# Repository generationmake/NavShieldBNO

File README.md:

# NavShieldBNO
Navigation shield for Arduino with Bosch BNO055, BNO080 or BNO085

## pin usage

### Arduino MKR connector CN1

| **Pin** | **Pin Name** | **Signal**    | **Description**                  |
|:-------:|:------------:|:-------------:|:--------------------------------:|
| 1       | AREF         |               |                                  |
| 2       | DAC0/A0      |               |                                  |
| 3       | A1           |               |                                  |
| 4       | A2           |               |                                  |
| 5       | A3           |               |                                  |
| 6       | A4           |               |                                  |
| 7       | A5           | WAKE_2        | option 2 for WAKE from BNO085    |
| 8       | A6           |               |                                  |
| 9       | 0            |               |                                  |
| 10      | 1            | WAKE_1        | option 1 for WAKE from BNO085    |
| 11      | 2            | BMP388_CS     | chip select for BMP388           |
| 12      | 3            |               |                                  |
| 13      | 4            |               |                                  |
| 14      | 5            | BNO085_CS     | chip select for BNO085           |
| 15      | 6            | BMP388_INT    | interrupt from BMP388            |
| 16      | 7            | BNO085_INT    | interrupt from BNO085            |
| 17      | 8/MOSI       | SPI_MOSI      | to sensors if SPI option is used |
| 18      | 9/SCK        | SPI_SCK       | to sensors if SPI option is used |
| 19      | 10/MISO      | SPI_MISO      | to sensors if SPI option is used |
| 20      | 11/SDA       | I2C_SDA       | to sensors if I2C option is used |
| 21      | 12/SCL       | I2C_SCL       | to sensors if I2C option is used |
| 22      | 13/RX        | SERIAL_RX     | to connector CN3                 |
| 23      | 14/TX        | SERIAL_TX     | to connector CN3                 |
| 24      | RESET        | RESET         | Reset for BNO085                 |
| 25      | GND          | GND           |                                  |
| 26      | VCC          | 3V3-rail      | supply voltage for board         |
| 27      | VIN          |               |                                  |
| 28      | 5V0          |               |                                  |

### Qwiic I2C connector CN2

compatible to Sparkfun Qwiic. JST SH 1mm 4-pin.

| **Pin** | **Signal**    | **Description**                  |
|:-------:|:-------------:|:--------------------------------:|
| 1       | GND           |                                  |
| 2       | VCC           |                                  |
| 3       | I2C_SDA       |                                  |
| 4       | I2C_SCL       |                                  |

### serial connector CN3

JST SH 1mm 4-pin.

| **Pin** | **Signal**    | **Description**                  |
|:-------:|:-------------:|:--------------------------------:|
| 1       | GND           |                                  |
| 2       | VCC           |                                  |
| 3       | SERIAL_TX     |                                  |
| 4       | SERIAL_RX     |                                  |

## PCB

### Top

### Bottom

## Variants

It is possible to mount a BNO055 instead of the BNO085. The BNO055 only supports the I2C interface.

### BOM changes

The following parts need to be changed:

| part | BNO085 variant | BNO055 variant |
|:----:|:--------------:|:--------------:|
| R1   | 10k            | DNI            |
| R2   | 10k            | DNI            |
| R5   | 10k            | DNI            |
| R6   | DNI            | 10k            |
| R7   | 10k            | DNI            |
| R8   | DNI            | 10k            |
| R10  | DNI            | 0R             |
| R11  | DNI            | 0R             |
| R12  | DNI            | 0R             |
| R13  | 0R             | DNI            |
| R14  | 0R             | DNI            |
| R15  | 0R             | DNI            |
| R16  | 0R             | DNI            |
| C8   | 100nF          | DNI            |
| C9   | 100nF          | DNI            |
| C10  | 100nF          | DNI            |
| C11  | 100nF          | DNI            |
| U1   | BNO085         | BMP055         |
| U3   | BMP280         | DNI            |
| U4   | BME280         | DNI            |
| U5   | VCNL4040       | DNI            |

## Resources

### Datasheets

 * *BNO080* https://cdn.sparkfun.com/assets/2/b/9/0/6/DS-14686-BNO080.pdf
 * *BMP388* https://www.bosch-sensortec.com/media/boschsensortec/downloads/datasheets/bst-bmp388-ds001.pdf
 * *BNO055* https://www.bosch-sensortec.com/media/boschsensortec/downloads/datasheets/bst-bno055-ds000.pdf

### Arduino Libraries

* [107-Arduino-BNO085](https://github.com/107-systems/107-Arduino-BNO085)
* [107-Arduino-BMP388](https://github.com/107-systems/107-Arduino-BMP388)

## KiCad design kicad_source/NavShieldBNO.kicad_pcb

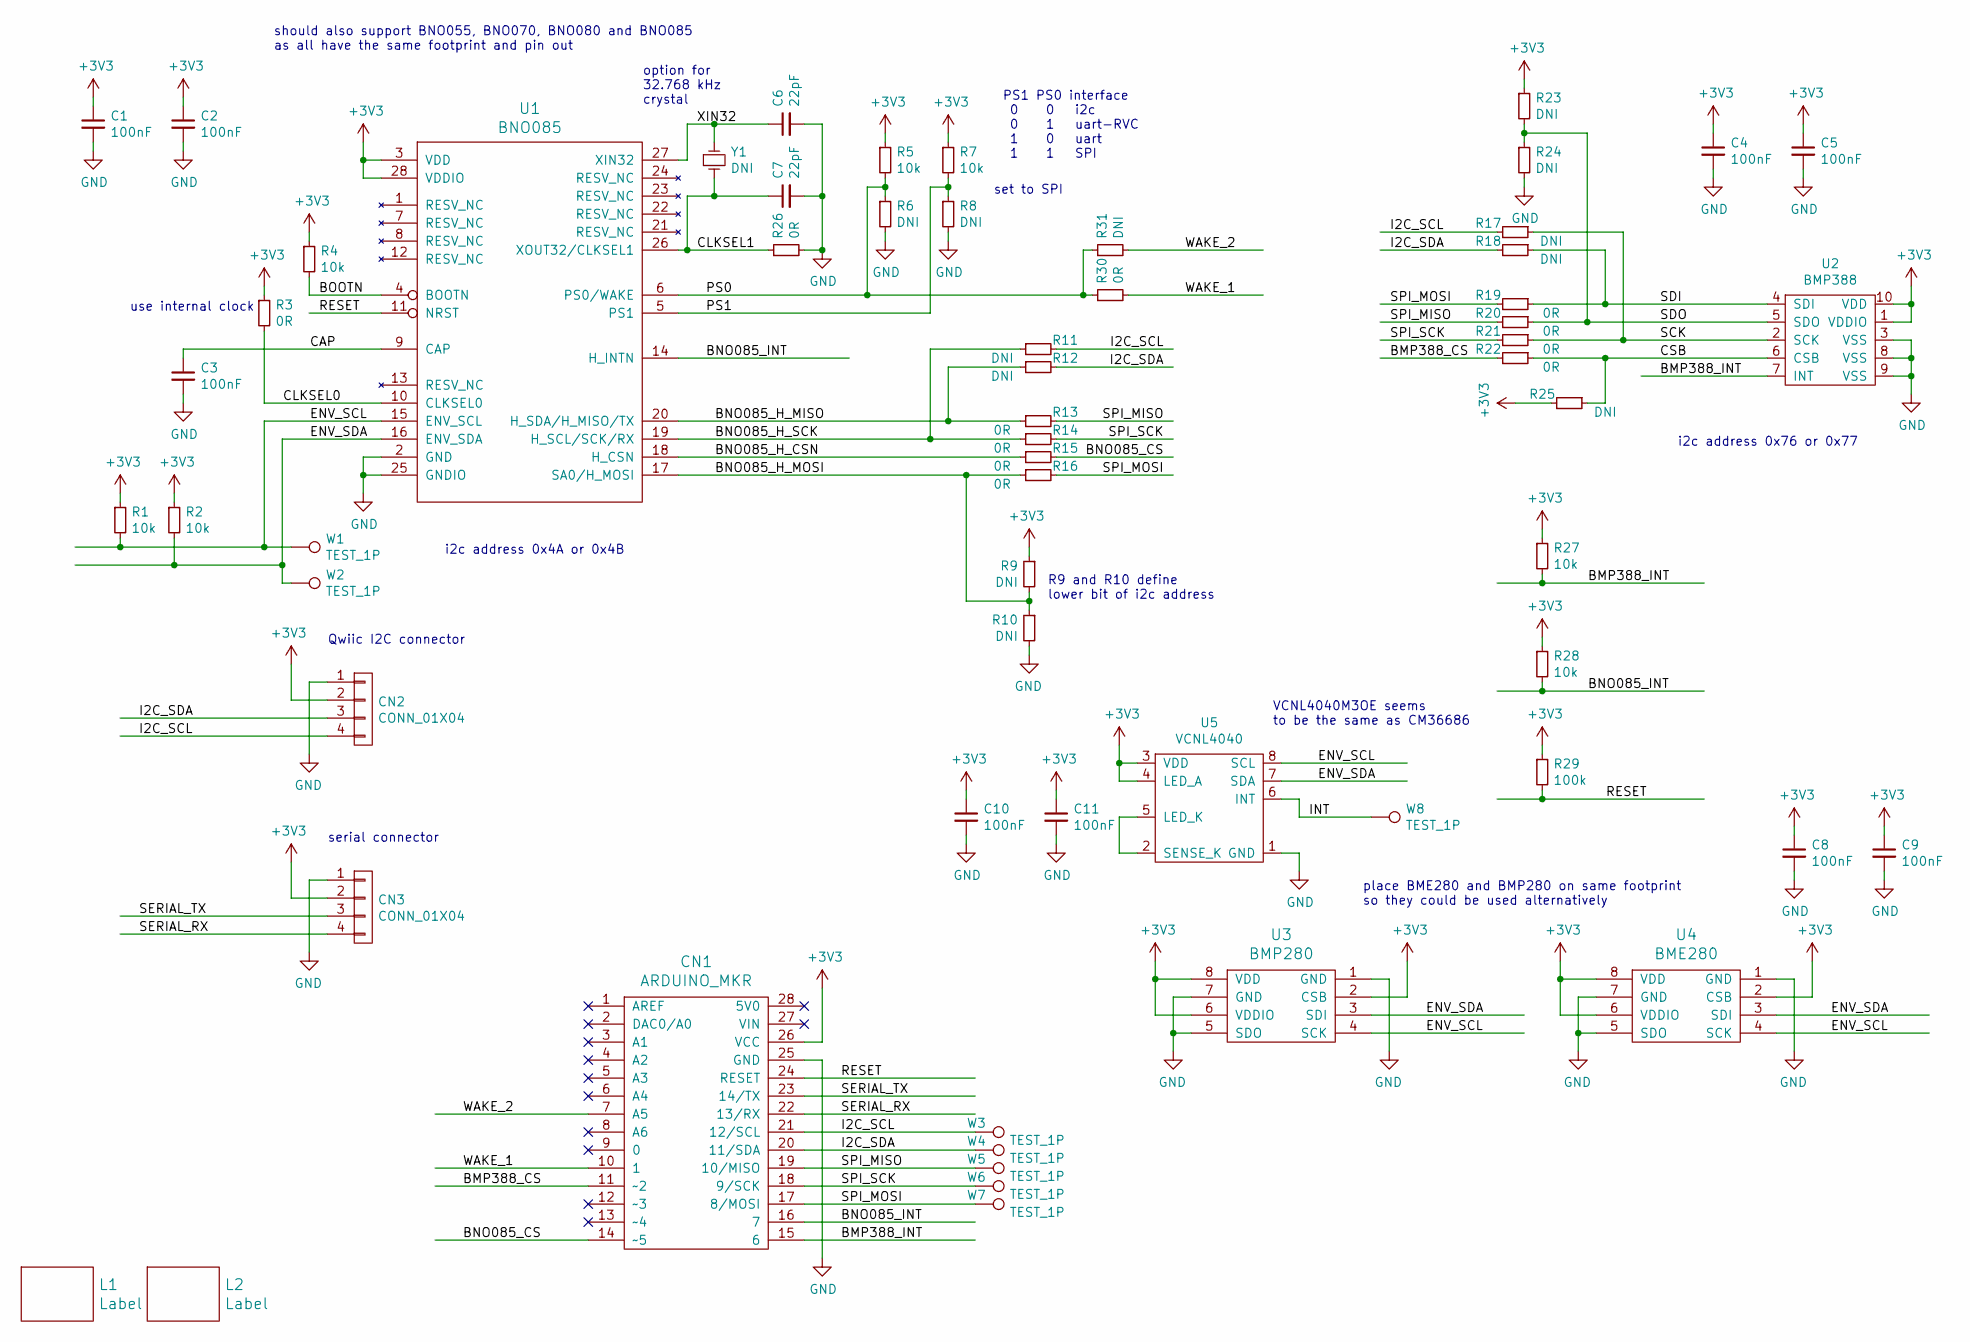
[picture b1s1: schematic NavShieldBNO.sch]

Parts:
C1, C2, C3, C4, C5, C8, C9, C10, C11: 100nF; C_0603
C6, C7: 22pF; C_0603
CN1: ARDUINO_MKR; ARDUINO_MKR_HOLES
CN2, CN3: CONN_01X04; Connectors_JST_SM04B-SRSS-TB
L1: Label; generationmake_small_solder
L2: Label; generationmake_logo
R1, R2, R4, R5, R7, R27, R28: 10k; R_0603
R3, R13, R14, R15, R16, R19, R20, R21, R22, R26, R30: 0R; R_0603
R6, R8, R9, R10, R11, R12, R17, R18, R23, R24, R25, R31: DNI; R_0603
R29: 100k; R_0603
U1: BNO085; LGA-28-5832
U2: BMP388
U3: BMP280
U4: BME280
U5: VCNL4040
W1, W2, W3, W4, W5, W6, W7, W8: TEST_1P; SolderWirePad_single_1mmSMD
Y1: DNI; Crystal_SMD_3.2x1.5mm_2Pad

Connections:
+3V3: C1.1, C2.1, C4.1, C5.1, C8.1, C9.1, C10.1, C11.1, CN1.26 (VCC), CN2.2, CN3.2, R1.1, R2.1, R3.1, R4.1, R5.1, R7.1, R9.1, R23.1, R25.2, R27.1, R28.1, R29.1, U1.3 (VDD), U1.28 (VDDIO), U2.1 (VDDIO), U2.10 (VDD), U3.2 (CSB), U3.6 (VDDIO), U3.8 (VDD), U4.2 (CSB), U4.6 (VDDIO), U4.8 (VDD), U5.3 (VDD), U5.4 (LED_A)
/BMP388_CS: CN1.11 (~~2), R22.2
/BMP388_INT: CN1.15 (6), R27.2, U2.7 (INT)
/BNO085_CS: CN1.14 (~~5), R15.2
/BNO085_H_CSN: R15.1, U1.18 (H_CSN)
/BNO085_H_MISO: R12.1, R13.1, U1.20 (H_SDA/H_MISO/TX)
/BNO085_H_MOSI: R9.2, R10.1, R16.1, U1.17 (SA0/H_MOSI)
/BNO085_H_SCK: R11.1, R14.1, U1.19 (H_SCL/SCK/RX)
/BNO085_INT: CN1.16 (7), R28.2, U1.14 (H_INTN)
/BOOTN: R4.2, U1.4 (BOOTN)
/CAP: C3.1, U1.9 (CAP)
/CLKSEL0: R3.2, U1.10 (CLKSEL0)
/CLKSEL1: C7.1, R26.1, U1.26 (XOUT32/CLKSEL1), Y1.2
/CSB: R22.1, R25.1, U2.6 (CSB)
/ENV_SCL: R1.2, U1.15 (ENV_SCL), U3.4 (SCK), U4.4 (SCK), U5.8 (SCL), W1.1
/ENV_SDA: R2.2, U1.16 (ENV_SDA), U3.3 (SDI), U4.3 (SDI), U5.7 (SDA), W2.1
/I2C_SCL: CN1.21 (12/SCL), CN2.4, R11.2, R17.2, W3.1
/I2C_SDA: CN1.20 (11/SDA), CN2.3, R12.2, R18.2, W4.1
/INT: U5.6 (INT), W8.1
/PS0: R5.2, R6.1, R30.1, R31.1, U1.6 (PS0/WAKE)
/PS1: R7.2, R8.1, U1.5 (PS1)
/RESET: CN1.24 (RESET), R29.2, U1.11 (NRST)
/SCK: R17.1, R21.1, U2.2 (SCK)
/SDI: R18.1, R19.1, U2.4 (SDI)
/SDO: R20.1, R23.2, R24.1, U2.5 (SDO)
/SERIAL_RX: CN1.22 (13/RX), CN3.4
/SERIAL_TX: CN1.23 (14/TX), CN3.3
/SPI_MISO: CN1.19 (10/MISO), R13.2, R20.2, W5.1
/SPI_MOSI: CN1.17 (8/MOSI), R16.2, R19.2, W7.1
/SPI_SCK: CN1.18 (9/SCK), R14.2, R21.2, W6.1
/WAKE_1: CN1.10 (1), R30.2
/WAKE_2: CN1.7 (A5), R31.2
/XIN32: C6.1, U1.27 (XIN32), Y1.1
GND: C1.2, C2.2, C3.2, C4.2, C5.2, C6.2, C7.2, C8.2, C9.2, C10.2, C11.2, CN1.25 (GND), CN2.1, CN3.1, R6.2, R8.2, R10.2, R24.2, R26.2, U1.2 (GND), U1.25 (GNDIO), U2.3 (VSS), U2.8 (VSS), U2.9 (VSS), U3.1 (GND), U3.5 (SDO), U3.7 (GND), U4.1 (GND), U4.5 (SDO), U4.7 (GND), U5.1 (GND)
unnamed: U5.2 (SENSE_K), U5.5 (LED_K)

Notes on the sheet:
i2c address 0x76 or 0x77
set to SPI
use internal clock
i2c address 0x4A or 0x4B
should also support BNO055, BNO070, BNO080 and BNO085 as all have the same footprint and pin out
Qwiic I2C connector
serial connector
R9 and R10 define lower bit of i2c address
PS1 PS0 interface 0 0 i2c 0 1 uart-RVC 1 0 uart 1 1 SPI
option for 32.768 kHz crystal
place BME280 and BMP280 on same footprint so they could be used alternatively
VCNL4040M3OE seems to be the same as CM36686

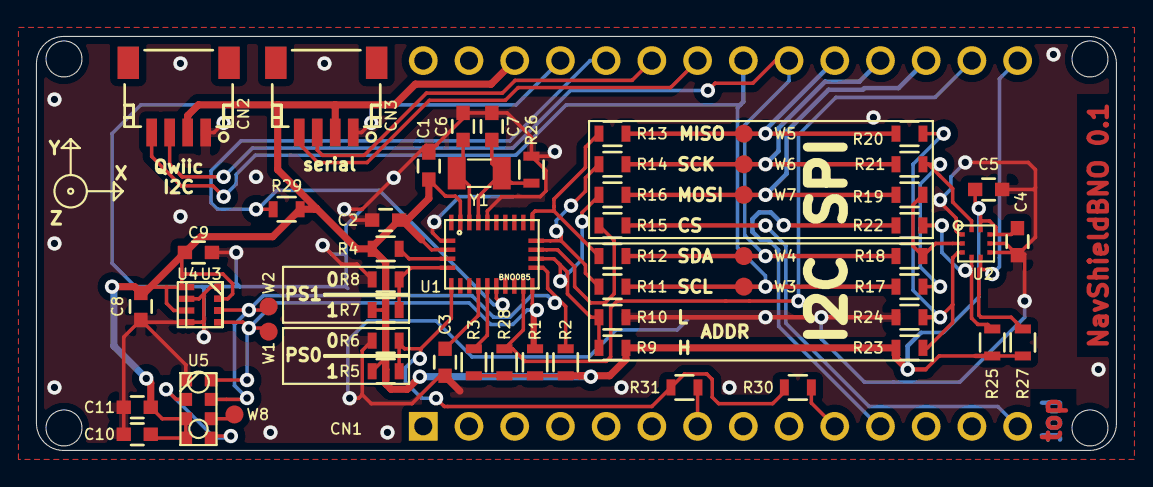
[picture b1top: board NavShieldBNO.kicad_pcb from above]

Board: 2 copper layers, 60.0 x 23.0 mm, 61 parts (1 on the bottom side), 35 nets.

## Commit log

2020-09-04 added kicad project
2020-09-06 updated schematic, added schematic pdf
2020-09-06 annotated schematic
2020-09-08 added pull up on INT and reset lines
2020-09-08 connected CLKSEL1 to GND via resistor
2020-09-09 moved BNO085_CS to D5, updated schematic pdf
2020-09-09 added links to datasheets
2020-09-15 Adding links to Arduino libraries for BNO085/BMP388
2020-09-16 added WAKE signal to Arduino connector
2020-09-16 added connector for I2C and serial
2020-09-16 started placement
2020-09-16 first draft of layout
2020-09-16 added images of PCBs
2020-09-16 updated readme with images
2020-09-17 updated schematic pdf
2020-09-22 made pcb bigger and added holes for Arduino MKR
2020-09-24 added second option for wake on A5, rearranged placement of option resistors and added description in silk screen
2020-09-25 added option for 32 kHz crystal, updated images and pdf
2020-09-27 added BME280/BMP280
2020-09-27 added Vishay VCNL4040
2020-09-27 added logo, updated images and pdf
2020-09-27 updated layout, made DRC, updated silk screen
2020-09-27 updated images
2020-11-22 updated some footprints with 3d models
2020-11-22 added image of variant, updated readme
2020-11-22 updated rendering of board
2020-11-22 added step file of board
2020-11-28 added pinout in readme
